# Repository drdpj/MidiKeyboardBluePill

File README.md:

# MidiKeyboardBluePill
This is software for the STM32F103 Microcontroller to convert serial midi into the outputs that would be generated by the Hybrid Music 4000 keyboard for the BBC Micro and BBC Master.

A BluePill board, plus optocoupler circuit is all that is required to get this to work, however there is a complete hardware design too which incorporates MIDI-through and blinkenlights.

  Pins used: Userport PB0-7 (even pins 6-20) are on GPIOs PB4,6-12
  Userport CB1 (pin 2) -> Clk, GPIO PB13  (SPI2) - add external 10k pullup to 5V
  Userport CB2 (pin 4) -> MOSI, GPIO PB15 (SPI2)
  MIDI serial in (3.3V) -> GPIO PA3  (USART2)
  PA5 - Button (to ground) to program channel (press once and next note sets the channel, press twice and channel is ignored),
  PA4 - LED (active low, 560R to 3.3V) to indicate programming mode.

The circuit provided specifies a particular opto-isolator (which just happened to be the SMT part I had available) - you can use whatever circuit you like that fits with the midi 1.0 spec. I, and others, have had this working fine with a 6N138.

If you'd like to update the firmware on a pre-built unit, you'll need an st-link. If you have a nucleo development board, it has an ST-LINK V2 built in. Failing that, the very cheap £5 ones work fine (e.g. https://www.amazon.co.uk/DAOKAI-Downloader-Programmer-STM8STM32-Programming/dp/B09WVQNFNM), but they need to be used in conjunction with ST-LINK Utility rather than CubeProgrammer. It's available here: https://www.st.com/en/development-tools/stsw-link004.html

Connect GND to GND, SWCLK to SWCLK, SWDIO to SWDIO. Don't connect ANYTHING to +3.3V. 

n.b. This is the "debug" header on the recent boards, pin 1 is the right hand pin of the group of 4 if the text is the right way up.

Connect +5V to a +5V header if there is one on your board, or Pin 1 or 3 of the user port connector:

Download the latest release bin file, load into the ST-Link software, and then use the program option to re-flash and verify the unit. There are numerous guides to using the ST-Link software on the internet, so I won't repeat them here - a quick google should reveal them.

Presently I have a few standalone, fully built and tested units for sale. Get in touch if you're interested.

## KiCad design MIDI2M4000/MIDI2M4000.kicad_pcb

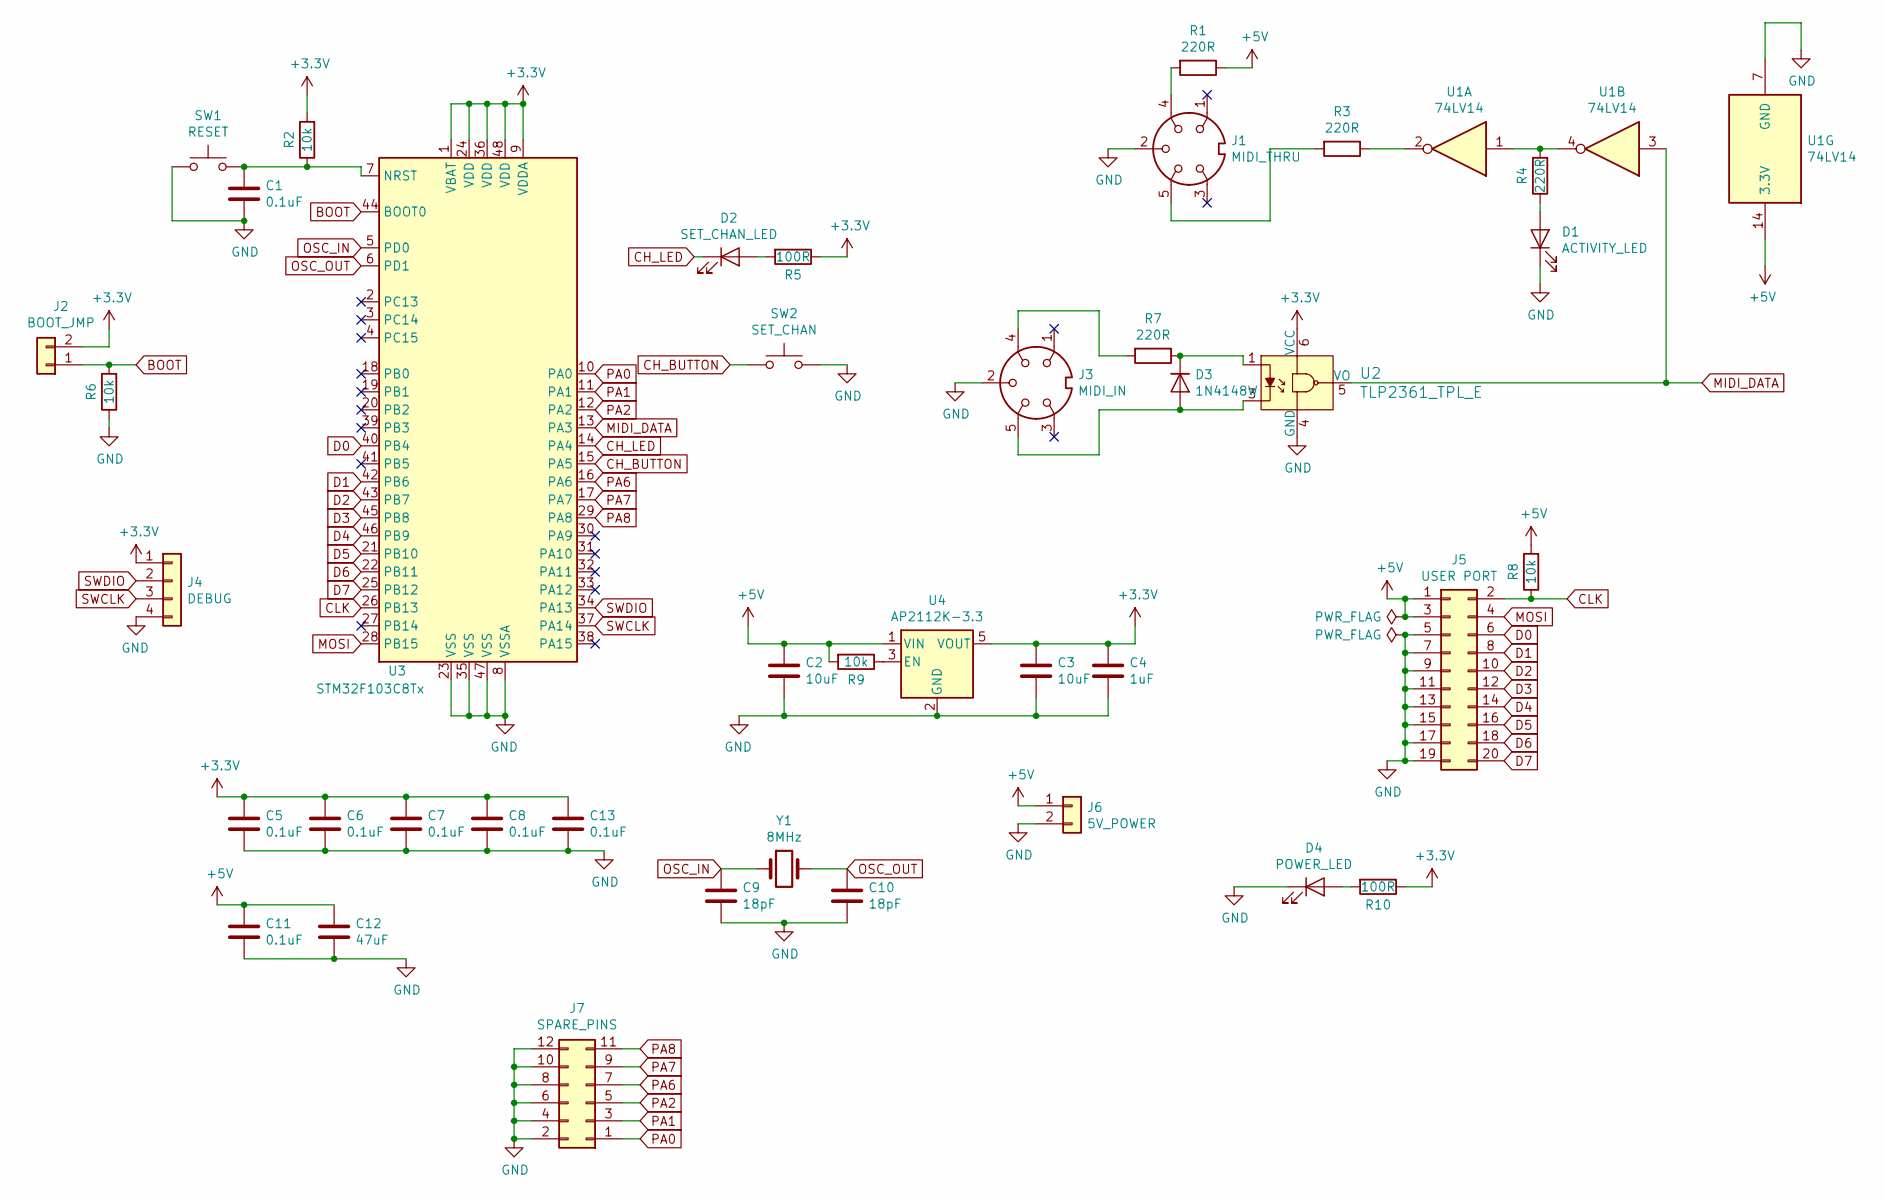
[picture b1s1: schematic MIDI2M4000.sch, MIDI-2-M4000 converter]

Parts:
C1, C5, C6, C7, C8, C11, C13: 0.1uF; C_0805_2012Metric
C2, C3: 10uF; C_0805_2012Metric
C4: 1uF; C_0805_2012Metric
C9, C10: 18pF; C_0805_2012Metric
C12: 47uF; C_0805_2012Metric
D1: ACTIVITY_LED; PinHeader_1x02_P2.54mm_Vertical
D2: SET_CHAN_LED; PinHeader_1x02_P2.54mm_Vertical
D3: 1N4148W; D_SOD-123
D4: POWER_LED; PinHeader_1x02_P2.54mm_Vertical
J1: MIDI_THRU; din_5_econet_pcb_mount
J2: BOOT_JMP; PinHeader_1x02_P2.54mm_Vertical
J3: MIDI_IN; din_5_econet_pcb_mount
J4: DEBUG; PinHeader_1x04_P2.54mm_Vertical
J5: USER PORT; IDC-Header_2x10_P2.54mm_Horizontal_Lock
J6: 5V_POWER; PinHeader_1x02_P2.54mm_Vertical
J7: SPARE_PINS; PinSocket_2x06_P2.54mm_Vertical
R1, R3, R4, R7: 220R; R_0805_2012Metric
R2, R6, R8, R9: 10k; R_0805_2012Metric
R5, R10: 100R; R_0805_2012Metric
SW1: RESET; PinHeader_1x02_P2.54mm_Vertical
SW2: SET_CHAN; PinHeader_1x02_P2.54mm_Vertical
U1: 74LV14; SOIC-14_3.9x8.7mm_P1.27mm
U2: TLP2361_TPL_E; SOIC-6-5_W4.55mm; MPN TLP2361(TPL,E; Digi-Key_PN TLP2361(TPLECT-ND
U3: STM32F103C8Tx; LQFP-48_7x7mm_P0.5mm
U4: AP2112K-3.3; SOT-23-5
Y1: 8MHz; Crystal_SMD_TXC_7A-2Pin_5x3.2mm

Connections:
+3V3: C3.1, C4.1, C5.1, C6.1, C7.1, C8.1, C13.1, J2.2, J4.1, R2.2, R5.1, R10.1, U2.6 (VCC), U3.1 (VBAT), U3.9 (VDDA), U3.24 (VDD), U3.36 (VDD), U3.48 (VDD), U4.5 (VOUT)
+5V: C2.1, C11.1, C12.1, J5.1, J5.3, J6.1, R1.1, R8.2, R9.2, U1.14 (3.3V), U4.1 (VIN)
BOOT: J2.1, R6.2, U3.44 (BOOT0)
CH_BUTTON: SW2.1, U3.15 (PA5)
CH_LED: D2.1 (K), U3.14 (PA4)
CLK: J5.2, R8.1, U3.26 (PB13)
D0: J5.6, U3.40 (PB4)
D1: J5.8, U3.42 (PB6)
D2: J5.10, U3.43 (PB7)
D3: J5.12, U3.45 (PB8)
D4: J5.14, U3.46 (PB9)
D5: J5.16, U3.21 (PB10)
D6: J5.18, U3.22 (PB11)
D7: J5.20, U3.25 (PB12)
GND: C1.2, C2.2, C3.2, C4.2, C5.2, C6.2, C7.2, C8.2, C9.2, C10.2, C11.2, C12.2, C13.2, D1.1 (K), D4.1 (K), J1.2, J3.2, J4.4, J5.5, J5.7, J5.9, J5.11, J5.13, J5.15, J5.17, J5.19, J6.2, J7.2, J7.4, J7.6, J7.8, J7.10, J7.12, R6.1, SW1.1, SW2.2, U1.7 (GND), U2.4 (GND), U3.8 (VSSA), U3.23 (VSS), U3.35 (VSS), U3.47 (VSS), U4.2 (GND)
MIDI_DATA: U1.3, U2.5 (VO), U3.13 (PA3)
MOSI: J5.4, U3.28 (PB15)
unnamed: C1.1, R2.1, SW1.2, U3.7 (NRST)
unnamed: D1.2 (A), R4.1
unnamed: D2.2 (A), R5.2
unnamed: D3.1 (K), R7.1, U2.1
unnamed: D3.2 (A), J3.5, U2.3
unnamed: D4.2 (A), R10.2
unnamed: J1.4, R1.2
unnamed: J1.5, R3.2
unnamed: J3.4, R7.2
unnamed: R3.1, U1.2
unnamed: R4.2, U1.1, U1.4
unnamed: R9.1, U4.3 (EN)
OSC_IN: C9.1, U3.5 (PD0), Y1.1
OSC_OUT: C10.1, U3.6 (PD1), Y1.2
PA0: J7.1, U3.10 (PA0)
PA1: J7.3, U3.11 (PA1)
PA2: J7.5, U3.12 (PA2)
PA6: J7.7, U3.16 (PA6)
PA7: J7.9, U3.17 (PA7)
PA8: J7.11, U3.29 (PA8)
SWCLK: J4.3, U3.37 (PA14)
SWDIO: J4.2, U3.34 (PA13)

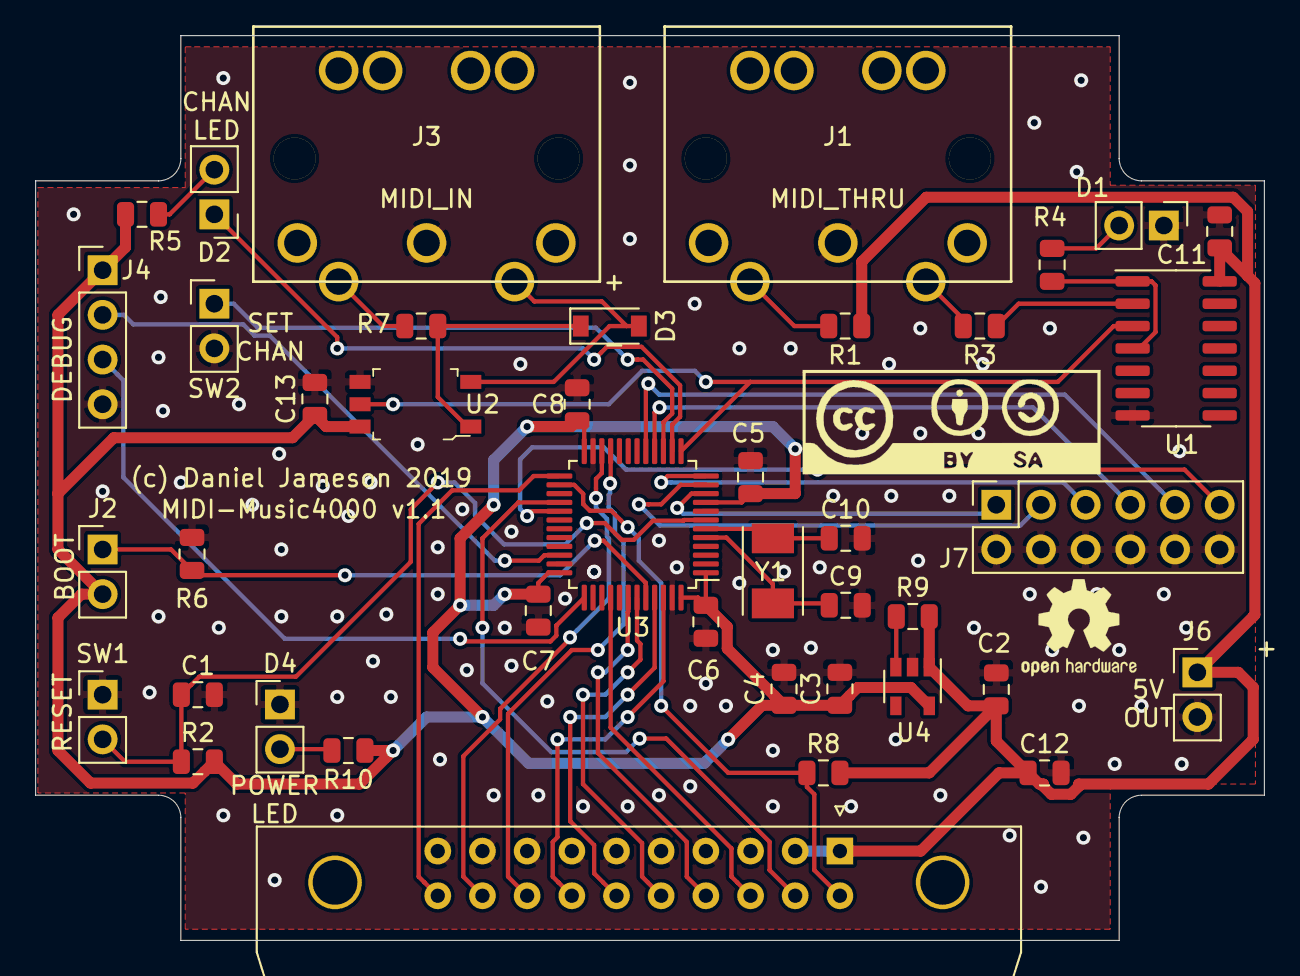
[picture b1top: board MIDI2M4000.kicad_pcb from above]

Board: 2 copper layers, 69.8 x 51.4 mm, 41 parts (0 on the bottom side), 39 nets.

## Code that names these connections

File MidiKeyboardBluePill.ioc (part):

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Mcu.Name=STM32F103C(8-B)Tx
Mcu.Package=LQFP48
Mcu.UserName=STM32F103C8Tx
PA13.Mode=Serial_Wire
PA13.Signal=SYS_JTMS-SWDIO
PA14.Mode=Serial_Wire
PA14.Signal=SYS_JTCK-SWCLK
PA2.Mode=Asynchronous
PA2.Signal=USART2_TX
PA3.Mode=Asynchronous
PA3.Signal=USART2_RX
PA4.GPIOParameters=PinState,GPIO_Label
PA4.GPIO_Label=program-led
PA4.PinState=GPIO_PIN_SET
PA4.Signal=GPIO_Output
PA5.GPIOParameters=GPIO_PuPd,GPIO_Label
PA5.GPIO_Label=button
PA5.GPIO_PuPd=GPIO_PULLUP
PA5.Signal=GPIO_Input
PB10.GPIOParameters=GPIO_Speed,PinState,GPIO_PuPd,GPIO_ModeDefaultOutputPP
PB10.GPIO_ModeDefaultOutputPP=GPIO_MODE_OUTPUT_PP
PB10.GPIO_PuPd=GPIO_NOPULL
PB10.GPIO_Speed=GPIO_SPEED_FREQ_MEDIUM
PB10.PinState=GPIO_PIN_SET
PB10.Signal=GPIO_Output
PB11.GPIOParameters=GPIO_Speed,PinState,GPIO_PuPd,GPIO_ModeDefaultOutputPP
PB11.GPIO_ModeDefaultOutputPP=GPIO_MODE_OUTPUT_PP
PB11.GPIO_PuPd=GPIO_NOPULL
PB11.GPIO_Speed=GPIO_SPEED_FREQ_MEDIUM
PB11.PinState=GPIO_PIN_SET
PB11.Signal=GPIO_Output
PB12.GPIOParameters=GPIO_Speed,PinState,GPIO_PuPd,GPIO_ModeDefaultOutputPP
PB12.GPIO_ModeDefaultOutputPP=GPIO_MODE_OUTPUT_PP
PB12.GPIO_PuPd=GPIO_NOPULL
PB12.GPIO_Speed=GPIO_SPEED_FREQ_MEDIUM
PB12.PinState=GPIO_PIN_SET
PB12.Signal=GPIO_Output
PB13.Mode=RX_Only_Simplex_Unidirect_Slave
PB13.Signal=SPI2_SCK
PB15.Mode=RX_Only_Simplex_Unidirect_Slave
PB15.Signal=SPI2_MOSI
PB4.GPIOParameters=GPIO_Speed,PinState,GPIO_PuPd,GPIO_ModeDefaultOutputPP
PB4.GPIO_ModeDefaultOutputPP=GPIO_MODE_OUTPUT_PP
PB4.GPIO_PuPd=GPIO_NOPULL
PB4.GPIO_Speed=GPIO_SPEED_FREQ_MEDIUM
PB4.PinState=GPIO_PIN_SET
PB4.Signal=GPIO_Output
PB6.GPIOParameters=GPIO_Speed,PinState,GPIO_PuPd,GPIO_ModeDefaultOutputPP
PB6.GPIO_ModeDefaultOutputPP=GPIO_MODE_OUTPUT_PP
PB6.GPIO_PuPd=GPIO_NOPULL
PB6.GPIO_Speed=GPIO_SPEED_FREQ_MEDIUM
PB6.PinState=GPIO_PIN_SET
PB6.Signal=GPIO_Output
PB7.GPIOParameters=GPIO_Speed,PinState,GPIO_PuPd,GPIO_ModeDefaultOutputPP
PB7.GPIO_ModeDefaultOutputPP=GPIO_MODE_OUTPUT_PP
PB7.GPIO_PuPd=GPIO_NOPULL
PB7.GPIO_Speed=GPIO_SPEED_FREQ_MEDIUM
PB7.PinState=GPIO_PIN_SET
PB7.Signal=GPIO_Output
PB8.GPIOParameters=GPIO_Speed,PinState,GPIO_PuPd,GPIO_ModeDefaultOutputPP
PB8.GPIO_ModeDefaultOutputPP=GPIO_MODE_OUTPUT_PP
PB8.GPIO_PuPd=GPIO_NOPULL
PB8.GPIO_Speed=GPIO_SPEED_FREQ_MEDIUM
PB8.PinState=GPIO_PIN_SET
PB8.Signal=GPIO_Output
PB9.GPIOParameters=GPIO_Speed,PinState,GPIO_PuPd,GPIO_ModeDefaultOutputPP
PB9.GPIO_ModeDefaultOutputPP=GPIO_MODE_OUTPUT_PP
PB9.GPIO_PuPd=GPIO_NOPULL
PB9.GPIO_Speed=GPIO_SPEED_FREQ_MEDIUM
PB9.PinState=GPIO_PIN_SET
PB9.Signal=GPIO_Output
PD0-OSC_IN.Mode=HSE-External-Oscillator
PD0-OSC_IN.Signal=RCC_OSC_IN
PD1-OSC_OUT.Mode=HSE-External-Oscillator
PD1-OSC_OUT.Signal=RCC_OSC_OUT
RCC.SYSCLKFreq_VALUE=72000000
RCC.SYSCLKSource=RCC_SYSCLKSOURCE_PLLCLK
board=NUCLEO-F103RB

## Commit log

2019-05-25 Bluepill Version Checked
2019-05-26 Updated to use 5V tolerant GPIOs. Code commented in more detail.
2019-05-26 Tidying up formatting
2019-05-27 Removing unneeded files
2019-05-27 Starting to ignore build directory.
2019-05-29 All 5V tolerant inputs now, updated code to cope. Compiles fine with -O2, updated description of required hardware.
2019-06-01 Setting up some additional pins to allow channel selection (big cap doff to Jason for the implementation!)
2019-06-09 Select midi channel with pushbutton. Starts in "ignore channel" mode.
2019-06-09 Readme updated
2019-06-09 Implemented software debounce for channel select button.
2019-06-25 Adding PCB Design - CC-BY-SA 4.0
2019-06-26 Create LICENSE
2019-06-28 Added another decoupler for optoisolator.
2019-06-29 Logos back on PCB
2019-07-17 Shrunk PCB, v1.1
2019-08-12 Revised LED Resistor Values
2023-01-17 Ignore file
2023-01-18 Major update - midi processing to state machine, new HAL
2023-01-18 Tidying up, deal with more control commands
2023-01-20 Reset clocks in .ioc file.
2023-01-21 Update README.md
    Re-flashing instructions.
2024-04-27 Changes to the state machine.
2024-04-27 Get rid of some spurious returns...

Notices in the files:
MIDI2M4000/MIDI2M4000.kicad_pcb:
(c) Daniel Jameson 2019 CC-BY-SA 4.0
MIDI2M4000/MIDI2M4000.sch:
(c) 2019 Daniel Jameson
License: CC-BY-SA 4.0
